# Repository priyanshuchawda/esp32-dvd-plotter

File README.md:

# ESP32 / Uno DVD Pen Plotter

DVD-drive sleds on an **HW-130 L293D** shield. Both boards are supported in
separate folders — swap hardware, keep the same G-code tools.

| Doc | Contents |
| --- | --- |
| [`docs/STATUS.md`](docs/STATUS.md) | Done vs left checklist |
| [`docs/ARCHITECTURE.md`](docs/ARCHITECTURE.md) | How the system fits together |
| [`FINDINGS.md`](FINDINGS.md) | Measured bed, steps/mm, coil ohms |
| [`hardware/WIRING.md`](hardware/WIRING.md) | **ESP32 jumper wiring** (no soldering) |
| [`cad/pcb/`](cad/pcb/) | **ESP32↔HW-130 adapter PCB** (Uno-style stack + Gerbers) |
| [`src/README.md`](src/README.md) | Firmware folder map |

## Firmware folders

| Path | Board |
| --- | --- |
| [`src/uno/uno_plotter`](src/uno/uno_plotter/) | Arduino Uno (shield stacked) |
| [`src/esp32/esp32_plotter`](src/esp32/esp32_plotter/) | ESP32 (jumpers into shield headers) |

Bed: **55 × 50 mm** · steps/mm: **2.058** · baud: **115200**

## ESP32 quick start (current focus)

1. Shield **off** the Uno. Power shield `5V`+`GND` and `EXT_PWR` (yellow jumper
   off). Common GND with ESP32. See [`hardware/WIRING.md`](hardware/WIRING.md).
2. Eight jumpers: D12/D4/D7/D8 + D11/D3/D6/D5 → ESP32 GPIOs in the wiring table.
3. Flash and test:

```bash
arduino-cli compile -b esp32:esp32:esp32 src/esp32/esp32_plotter
arduino-cli upload  -b esp32:esp32:esp32 -p /dev/ttyUSB0 src/esp32/esp32_plotter

# USB serial: $COILTEST then raise $POWER= if needed
tools/send_gcode.py -p /dev/ttyUSB0 -b 115200 test-square-uno.gcode
```

Wi-Fi hotspot `DVD-Plotter` / `plotter123` → draw in the browser.

## Uno quick start

```bash
arduino-cli compile -b arduino:avr:uno src/uno/uno_plotter
arduino-cli upload  -b arduino:avr:uno -p /dev/ttyACM0 src/uno/uno_plotter
tools/send_gcode.py -p /dev/ttyACM0 -b 115200 test-square-uno.gcode
```

## Making G-code

| Tool | Use |
| --- | --- |
| [`tools/text2gcode.py`](tools/text2gcode.py) | Hershey single-stroke text |
| [`tools/handwriting2gcode.py`](tools/handwriting2gcode.py) | Neural handwriting |
| [`tools/image2gcode.py`](tools/image2gcode.py) | Bitmap → outlines |
| [`tools/send_gcode.py`](tools/send_gcode.py) | USB stream |
| `python3 sim/simulate.py job.gcode --paper` | Paper preview |

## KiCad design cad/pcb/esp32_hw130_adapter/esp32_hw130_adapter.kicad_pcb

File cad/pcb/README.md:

# ESP32 ↔ HW-130 adapter PCB

Uno-form adapter so the **HW-130 stacks like on an Arduino Uno**, while the
**ESP32-DevKit** plugs in beside it (right wing — not under the shield).

| | |
| --- | --- |
| KiCad project | [`esp32_hw130_adapter/`](esp32_hw130_adapter/) |
| Regenerator | [`generate_adapter.py`](generate_adapter.py) |
| Gerbers | [`out/gerbers.zip`](out/gerbers.zip) |
| Preview | [`out/adapter_top.png`](out/adapter_top.png) |
| Pin map | [`out/pinmap.md`](out/pinmap.md) |
| BOM | [`BOM.md`](BOM.md) |

**Board size ≈ 121 × 94 mm · 2-layer · DRC clean (0 errors)**

## How it works

```text
┌─────────────────────────────┬──────────────────────┐
│  Arduino R3 male headers    │  ESP32 DevKit        │
│  HW-130 stacks here         │  2×15 female sockets │
│  (same as Uno)              │  USB ↑               │
│                             │                      │
│  J_5V ── external 5 V       │                      │
└─────────────────────────────┴──────────────────────┘
```

Traces match firmware [`src/esp32/esp32_plotter`](../../src/esp32/esp32_plotter/):

| Shield | ESP32 |
| --- | --- |
| D12 | GPIO18 |
| D4 | GPIO19 |
| D7 | GPIO23 |
| D8 | GPIO13 |
| D11 | GPIO25 |
| D3 | GPIO26 |
| D6 | GPIO27 |
| D5 | GPIO32 |
| D10 (SERVO_1) | GPIO33 |
| 5V / GND | J_5V only |

## Open / rebuild

```bash
# GUI
kicad cad/pcb/esp32_hw130_adapter/esp32_hw130_adapter.kicad_pro

# Regenerate PCB from script (needs KiCad’s python3.14 + pcbnew)
python3.14 cad/pcb/generate_adapter.py
```

## Order / assemble

1. Upload [`out/gerbers.zip`](out/gerbers.zip) to any PCB fab (JLCPCB, PCBWay, …).
2. Solder parts from [`BOM.md`](BOM.md).
3. Plug ESP32 into the wing; stack HW-130 on the left headers.
4. Remove yellow **PWR** jumper; motors on `EXT_PWR`; logic 5 V into **J_5V**.
5. Flash `src/esp32/esp32_plotter` and run `$COILTEST`.

Until the PCB arrives, use Dupont jumpers — same nets — see
[`hardware/WIRING.md`](../../hardware/WIRING.md).

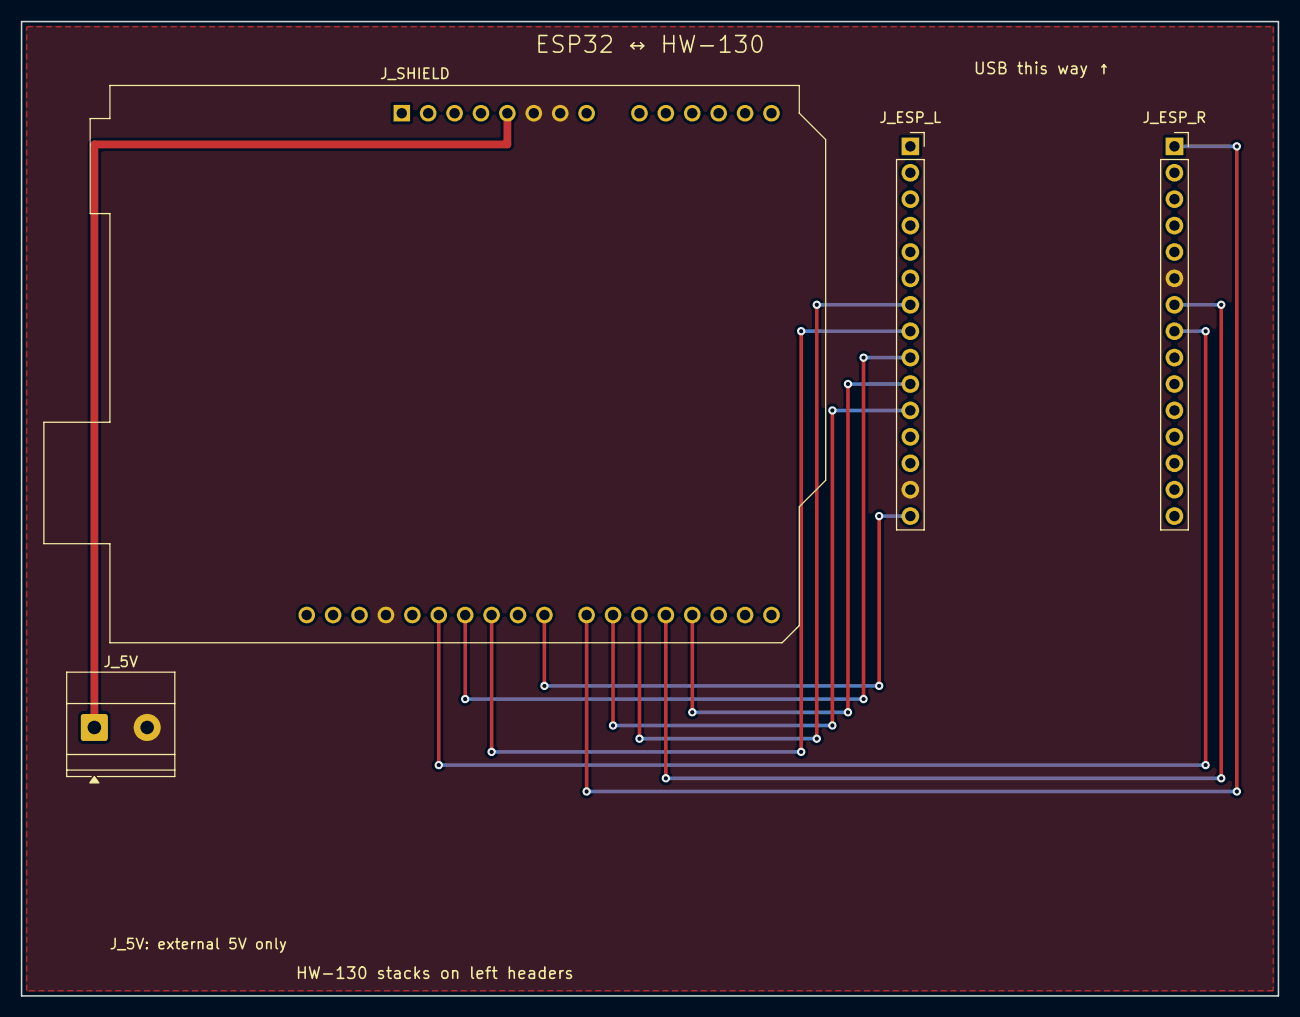
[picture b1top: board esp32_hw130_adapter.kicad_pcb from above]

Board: 2 copper layers, 120.9 x 93.7 mm, 4 parts (0 on the bottom side), 11 nets.

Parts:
J_5V: EXT_5V; TerminalBlock_Phoenix_MKDS-1,5-2-5.08_1x02_P5.08mm_Horizont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
J_ESP_L: DevKit_LEFT; PinSocket_1x15_P2.54mm_Vertical
J_ESP_R: DevKit_RIGHT; PinSocket_1x15_P2.54mm_Vertical
J_SHIELD: UNO_R3_HEADERS; Arduino_UNO_R3

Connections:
GND: J_5V.2, J_ESP_L.14, J_ESP_R.6, J_SHIELD.6, J_SHIELD.7, J_SHIELD.29
GPIO13: J_ESP_L.15, J_SHIELD.23
GPIO18: J_ESP_R.8, J_SHIELD.27
GPIO19: J_ESP_R.7, J_SHIELD.19
GPIO23: J_ESP_R.1, J_SHIELD.22
GPIO25: J_ESP_L.9, J_SHIELD.26
GPIO26: J_ESP_L.10, J_SHIELD.18
GPIO27: J_ESP_L.11, J_SHIELD.21
GPIO32: J_ESP_L.7, J_SHIELD.20
GPIO33: J_ESP_L.8, J_SHIELD.25
P5V: J_5V.1, J_SHIELD.5
